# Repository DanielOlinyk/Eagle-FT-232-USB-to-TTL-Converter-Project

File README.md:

# Eagle FT232 USB to TTL Converter Project
PCB design project of a power adapter that converts a plug in USB signal into a serial data signal for system processing.

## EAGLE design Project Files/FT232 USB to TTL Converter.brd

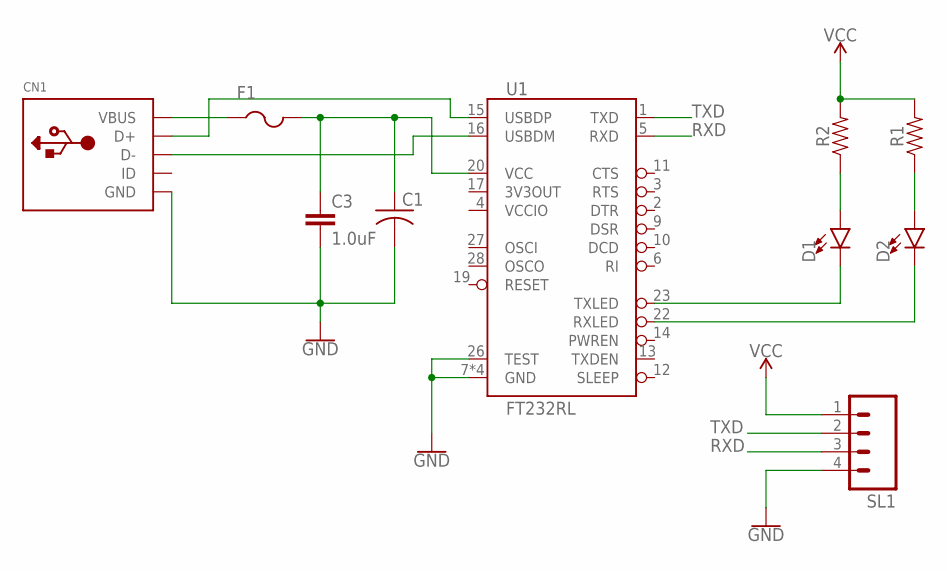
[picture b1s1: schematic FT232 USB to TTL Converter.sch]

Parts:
C1: C-USC1206; C1206
C3: 1.0uF; 1206
CN1: USBMOLEX; USB-MINIB-THM-MOLEX
D1, D2: LED1206; LED-1206
F1: PTCFUSE-1206; R1206
R1, R2: 1206
SL1: M04; 04P
U1: FT232RL; SSOP28DB

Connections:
GND: C1.2, C3.2, CN1.GND, SL1.4, U1.7 (GND), U1.18 (GND), U1.21 (GND), U1.25 (GND), U1.26 (TEST)
unnamed: CN1.VBUS, F1.1
unnamed: C1.1, C3.1, F1.2, U1.20 (VCC)
unnamed: CN1.D+, U1.15 (USBDP)
unnamed: CN1.D-, U1.16 (USBDM)
unnamed: D1.A, R2.1
unnamed: D2.A, R1.1
unnamed: D1.C, U1.23 (TXLED)
unnamed: D2.C, U1.22 (RXLED)
RXD: SL1.3, U1.5 (RXD)
TXD: SL1.2, U1.1 (TXD)
VCC: R1.2, R2.2, SL1.1
VCCIO: U1.4 (VCCIO)

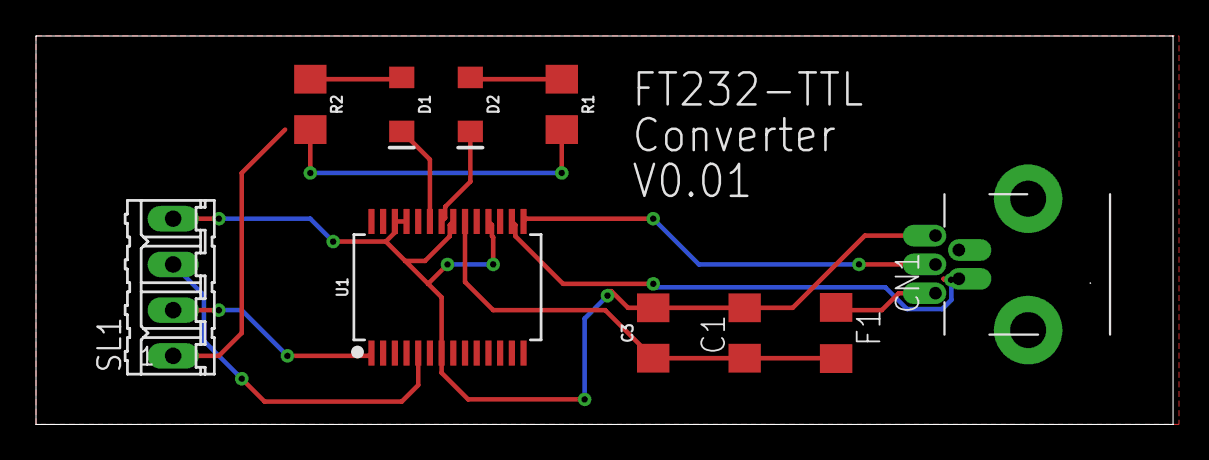
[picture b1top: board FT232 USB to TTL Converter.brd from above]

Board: 2 copper layers, 63.2 x 21.6 mm, 10 parts (0 on the bottom side), 12 nets.

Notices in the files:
parts and their libraries:
SparkFun-Capacitors: Licensing: Creative Commons ShareAlike 4.0 International - https://creativecommons.org/licenses/by-sa/4.0
